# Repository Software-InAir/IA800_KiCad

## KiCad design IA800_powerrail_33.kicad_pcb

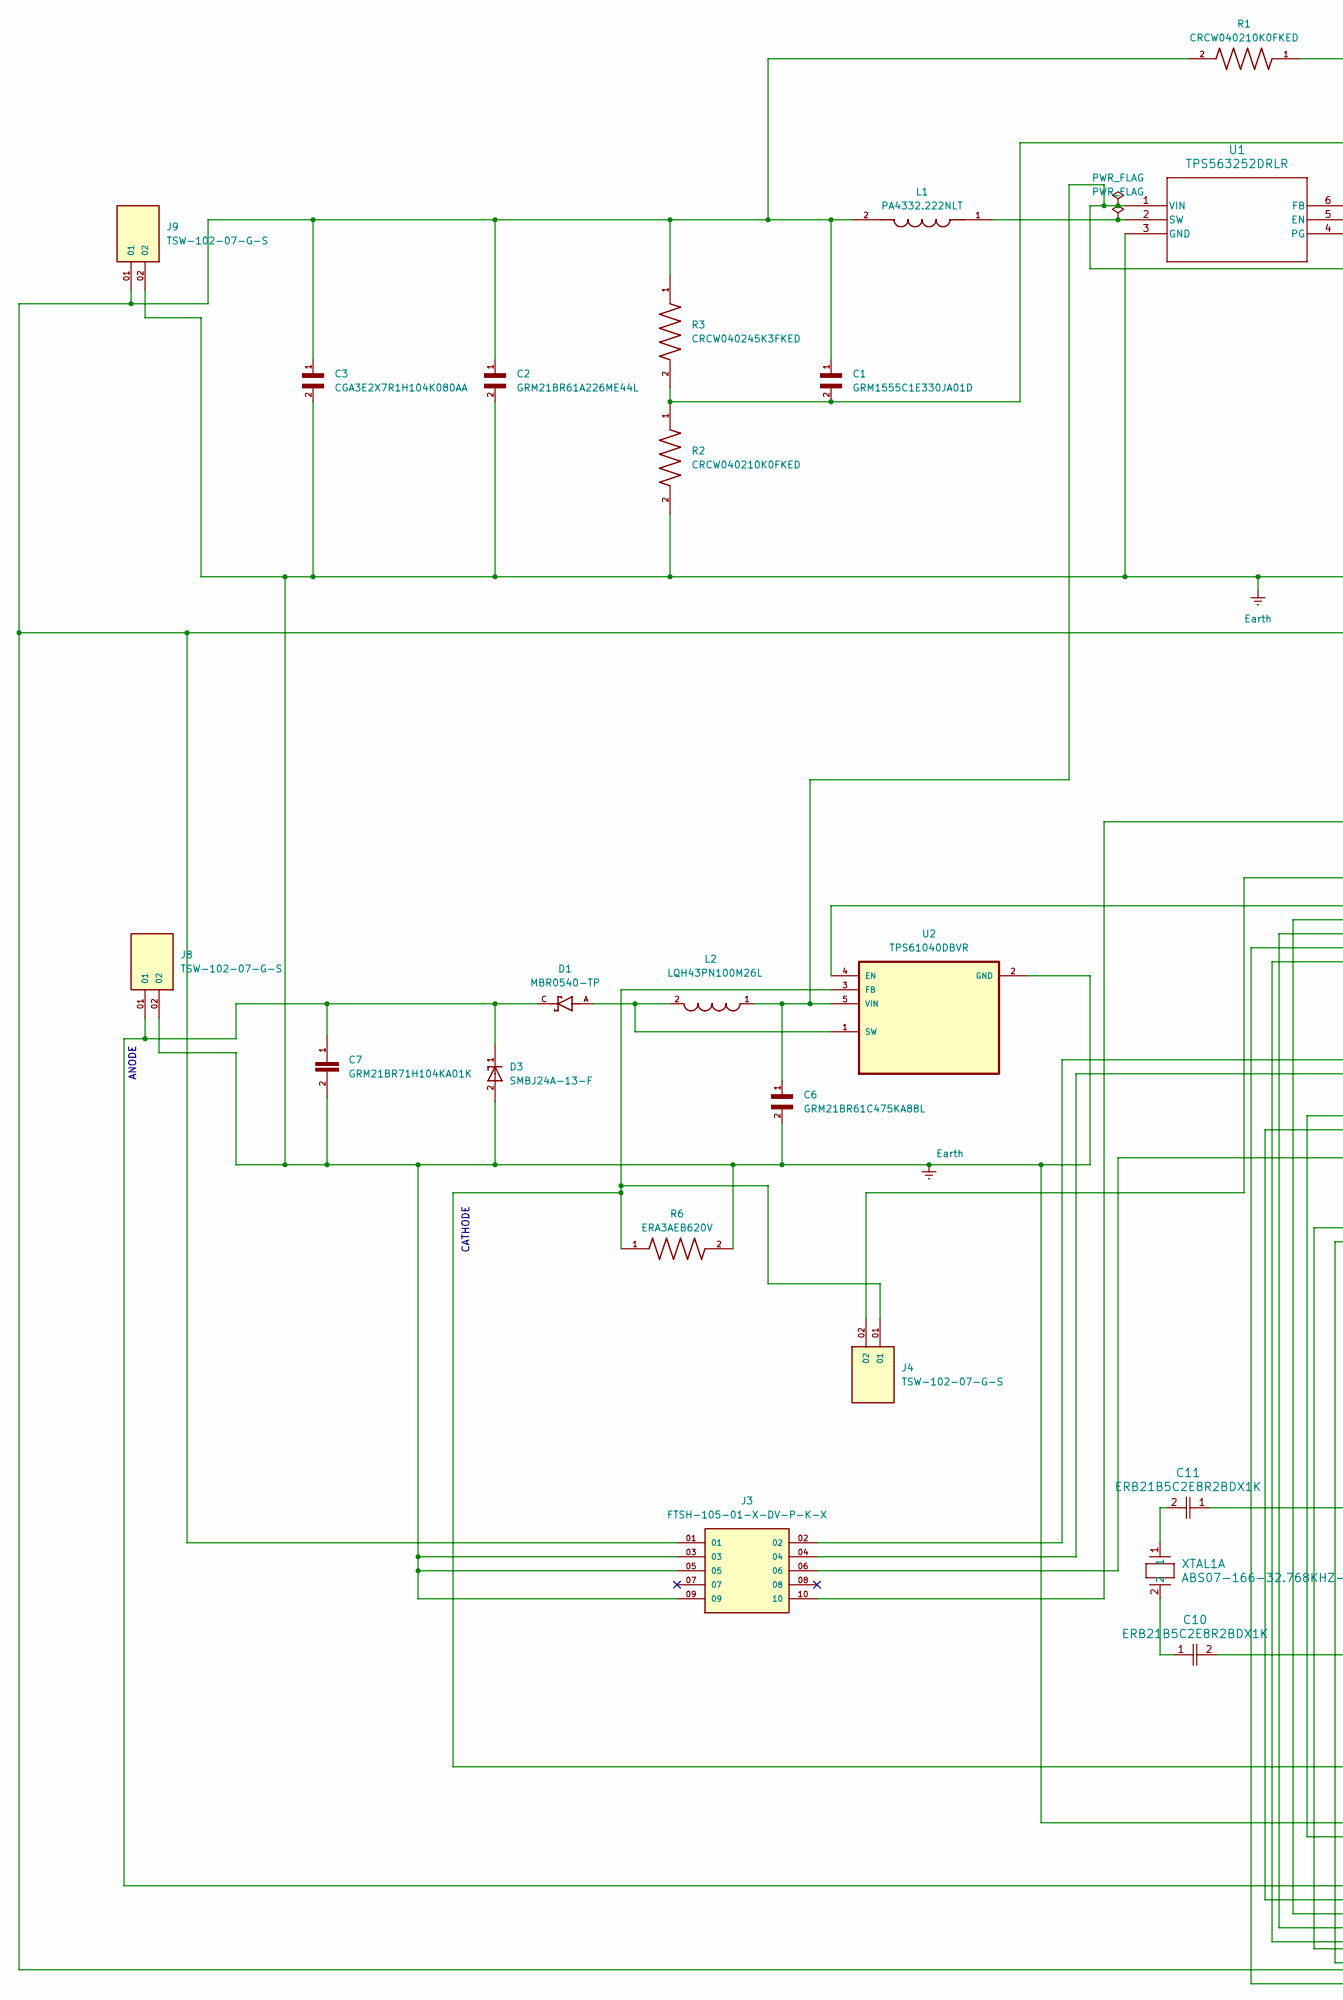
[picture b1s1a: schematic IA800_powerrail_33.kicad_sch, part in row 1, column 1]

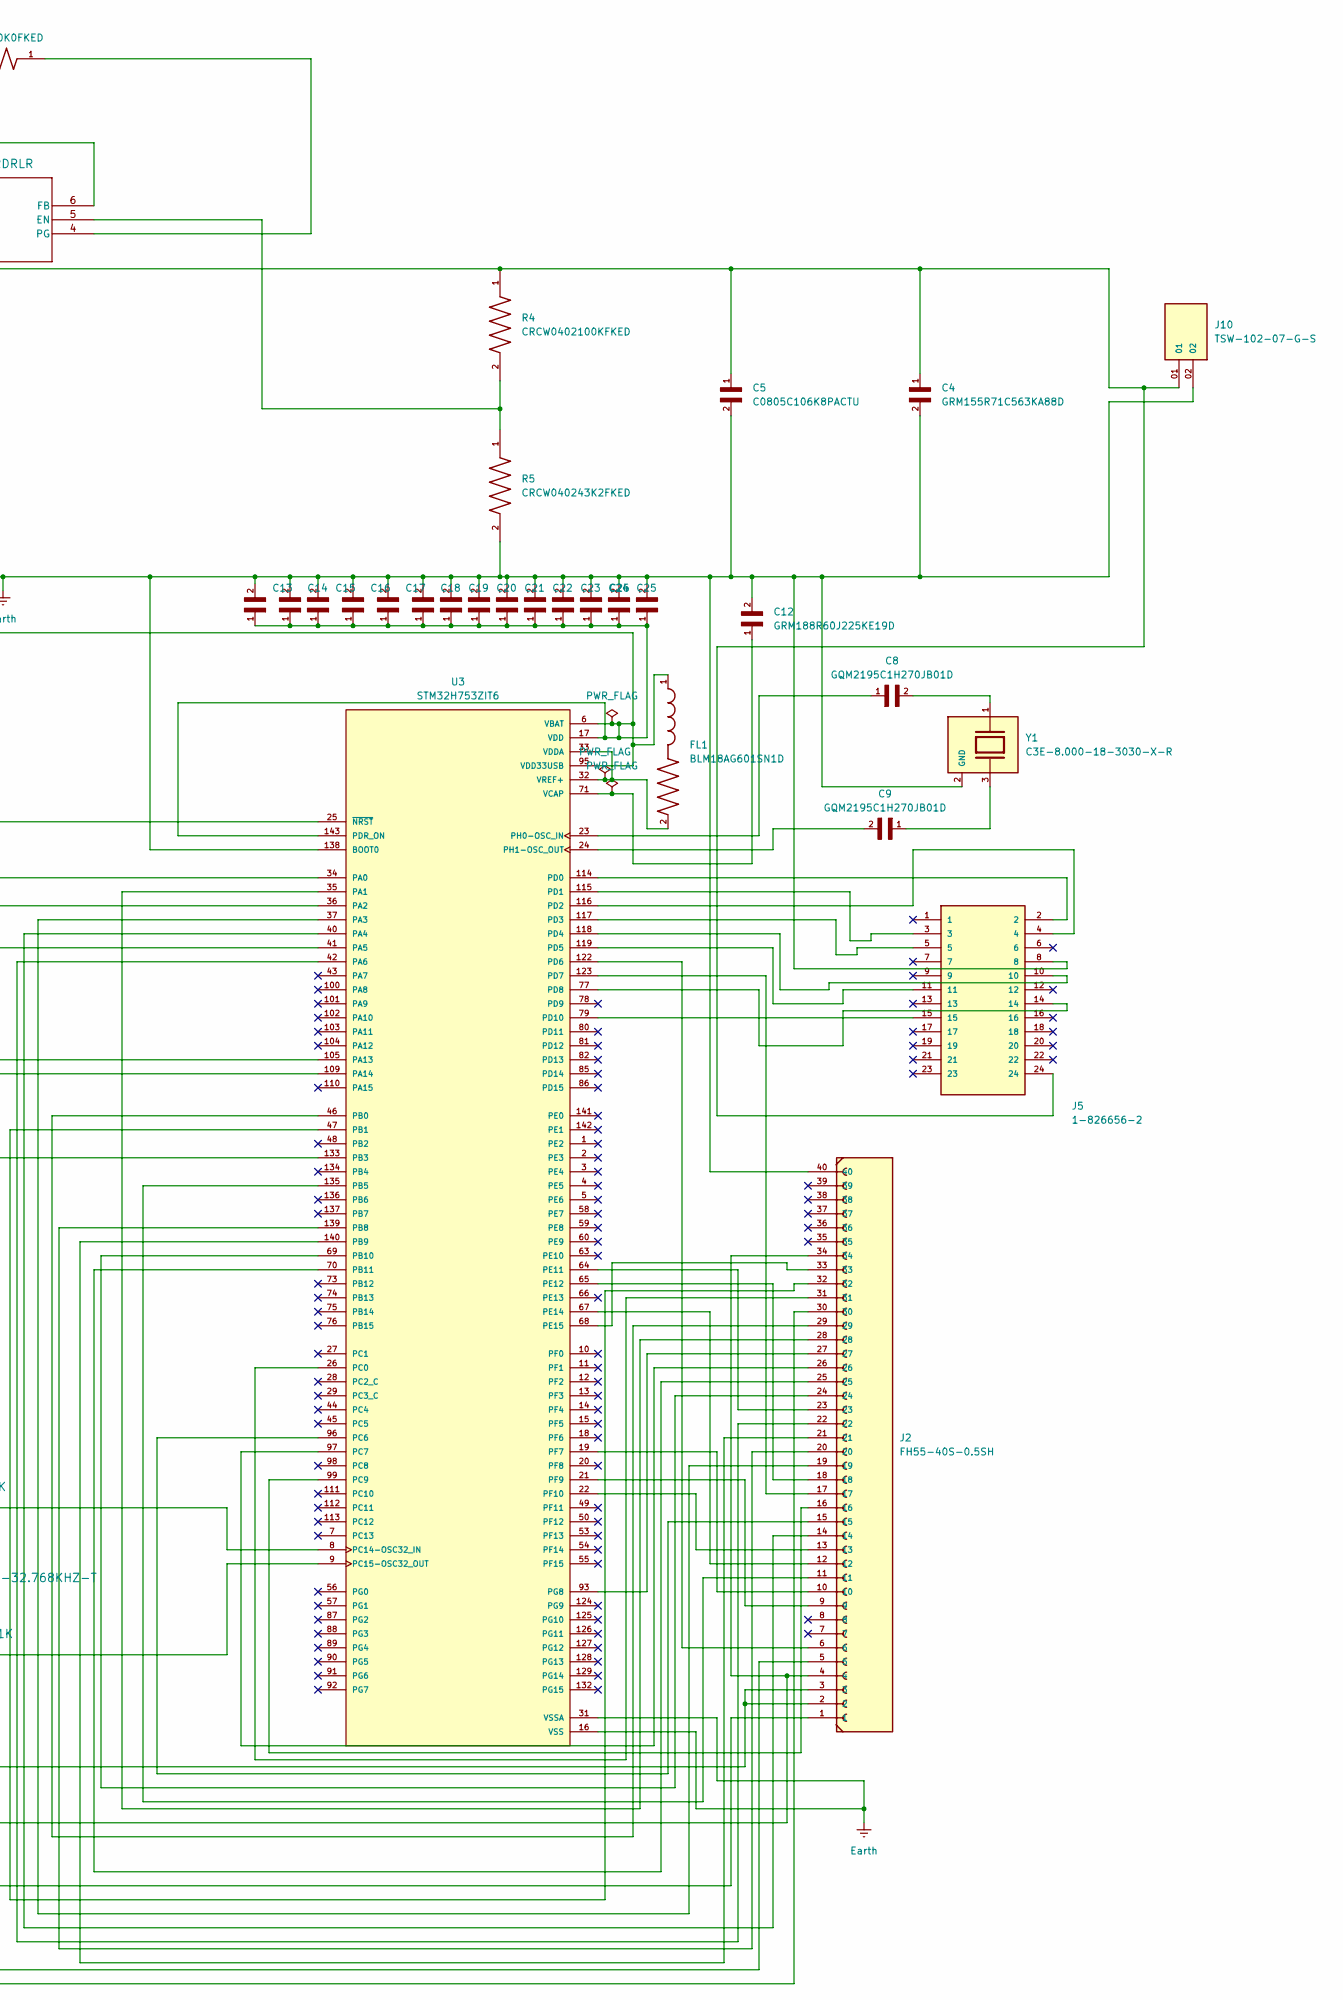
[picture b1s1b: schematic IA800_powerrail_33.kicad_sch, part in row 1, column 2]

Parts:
C1: GRM1555C1E330JA01D; CAPC1005X55N
C2: GRM21BR61A226ME44L; CAPC2012X145N
C3: CGA3E2X7R1H104K080AA; CAPC1608X90N
C4: GRM155R71C563KA88D; CAPC1005X55N
C5: C0805C106K8PACTU; CAPC2012X88N
C6: GRM21BR61C475KA88L; CAPC2012X135N
C7: GRM21BR71H104KA01K; CAPC2012X135
C8, C9: GQM2195C1H270JB01D; CAPC2012X95N
C10, C11: ERB21B5C2E8R2BDX1K; CAP_ERB21_MUR
C12: GRM188R60J225KE19D; CAPC1608X90N
C13, C14, C15, C16, C17, C18, C19, C20, C21, C22, C23, C24, C25, C26: CL05B104KO5NNNC; CAPC1005X55N
D1: MBR0540-TP; DIO_MBR0540-TP; PARTREV 3
D3: SMBJ24A-13-F; DIOM5336X250N; PARTREV 20 - 2
FL1: BLM18AG601SN1D; BEADC1608X95N
J2: FH55-40S-0.5SH; HRS_FH55-40S-0.5SH
J3: FTSH-105-01-X-DV-P-K-X; SAMTEC_FTSH-105-01-X-DV-P-K-X; PARTREV H
J4, J8, J9, J10: TSW-102-07-G-S; SAMTEC_TSW-102-07-G-S
J5: 1-826656-2; TE_1-826656-2; PARTREV R
L1: PA4332.222NLT; IND_PA4332.222NLT; PARTREV 12/23
L2: LQH43PN100M26L; IND_LQH43PN100M26L; PARTREV N/A
R1, R2: CRCW040210K0FKED; RESC1005X40N
R3: CRCW040245K3FKED; RESC1005X40N
R4: CRCW0402100KFKED; RESC1005X40N
R5: CRCW040243K2FKED; RESC1005X40N
R6: ERA3AEB620V; RES_ERA3AEB620V; PARTREV 3/1/2020
U1: TPS563252DRLR; SOT6_DRL_TEX
U2: TPS61040DBVR; SOT95P280X145-5N
U3: STM32H753ZIT6; QFP50P2200X2200X160-144N; PARTREV 7
XTAL1: ABS07-166-32.768KHZ-T; XTAL_ABS07-166-32.768KHZ-T_ABR
Y1: C3E-8.000-18-3030-X-R; XTAL_C3E-8.000-18-3030-X-R; PARTREV August 01, 2022

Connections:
Earth: C2.2, C3.2, C4.2, C5.2, C6.2, C7.2, C12.2, C13.2, C14.2, C15.2, C16.2, C17.2, C18.2, C19.2, C20.2, C21.2, C22.2, C23.2, C24.2, C25.2, C26.2, D3.2, J2.4, J2.34, J2.40, J3.03, J3.05, J3.09, J5.8, J8.02, J9.02, J10.02, R2.2, R5.2, R6.2, U1.3 (GND), U2.2 (GND), U3.16 (VSS), U3.31 (VSSA), U3.38 (VSS), U3.51 (VSS), U3.61 (VSS), U3.83 (VSS), U3.94 (VSS), U3.107 (VSS), U3.120 (VSS), U3.130 (VSS), U3.138 (BOOT0), Y1.2 (GND), Y1.4 (GND)
unnamed: C7.1, D1.C, D3.1, J2.1, J8.01
unnamed: C8.2, Y1.1
unnamed: C9.1, Y1.3
unnamed: C10.1, XTAL1.2
unnamed: C11.2, XTAL1.1
unnamed: R4.2, R5.1, U1.5 (EN)
unnamed: C1.2, R2.1, R3.2, U1.6 (FB)
unnamed: R1.1, U1.4 (PG)
unnamed: L1.1, U1.2 (SW)
unnamed: C4.1, C5.1, C6.1, J5.24, J10.01, L2.1, R4.1, U1.1 (VIN), U2.5 (VIN)
unnamed: U2.4 (EN), U3.36 (PA2)
unnamed: J2.2, J2.3, J4.01, R6.1, U2.3 (FB)
unnamed: D1.A, L2.2, U2.1 (SW)
unnamed: J4.02, U3.34 (PA0)
unnamed: J2.28, U3.35 (PA1)
unnamed: J2.19, U3.37 (PA3)
unnamed: J2.14, U3.40 (PA4)
unnamed: J2.30, U3.41 (PA5)
unnamed: J2.22, U3.42 (PA6)
unnamed: J3.02, U3.105 (PA13)
unnamed: J3.04, U3.109 (PA14)
unnamed: J2.29, U3.46 (PB0)
unnamed: J2.32, U3.47 (PB1)
unnamed: J3.06, U3.133 (PB3)
unnamed: J2.11, U3.135 (PB5)
unnamed: J2.20, U3.139 (PB8)
unnamed: J2.21, U3.140 (PB9)
unnamed: J2.24, U3.69 (PB10)
unnamed: J2.25, U3.70 (PB11)
unnamed: J2.31, U3.26 (PC0)
unnamed: J2.15, U3.96 (PC6)
unnamed: J2.26, U3.97 (PC7)
unnamed: J2.16, U3.99 (PC9)
unnamed: C11.1, U3.8 (PC14-OSC32_IN)
unnamed: C10.2, U3.9 (PC15-OSC32_OUT)
unnamed: J5.2, U3.114 (PD0)
unnamed: J5.3, U3.115 (PD1)
unnamed: J5.4, U3.116 (PD2)
unnamed: J5.5, U3.117 (PD3)
unnamed: J5.10, U3.118 (PD4)
unnamed: J5.11, U3.119 (PD5)
unnamed: J2.6, U3.122 (PD6)
unnamed: J2.17, U3.123 (PD7)
unnamed: J5.14, U3.77 (PD8)
unnamed: J5.15, U3.79 (PD10)
unnamed: J2.23, U3.64 (PE11)
unnamed: J2.18, U3.65 (PE12)
unnamed: J2.12, U3.67 (PE14)
unnamed: J2.33, U3.68 (PE15)
unnamed: J2.10, U3.19 (PF7)
unnamed: J2.9, U3.21 (PF9)
unnamed: J2.13, U3.22 (PF10)
unnamed: J2.27, U3.93 (PG8)
unnamed: C8.1, U3.23 (PH0-OSC_IN)
unnamed: C9.2, U3.24 (PH1-OSC_OUT)
unnamed: FL1.2, U3.32 (VREF+), U3.33 (VDDA)
unnamed: J3.10, U3.25 (~NRST)
VCAP: C12.1, U3.71 (VCAP), U3.106 (VCAP)
VDD: C1.1, C2.1, C3.1, C13.1, C14.1, C15.1, C16.1, C17.1, C18.1, C19.1, C20.1, C21.1, C22.1, C23.1, C24.1, C25.1, C26.1, FL1.1, J2.5, J3.01, J9.01, L1.2, R1.2, R3.1, U3.6 (VBAT), U3.17 (VDD), U3.30 (VDD), U3.39 (VDD), U3.52 (VDD), U3.62 (VDD), U3.72 (VDD), U3.84 (VDD), U3.95 (VDD33USB), U3.108 (VDD), U3.121 (VDD), U3.131 (VDD), U3.143 (PDR_ON), U3.144 (VDD)

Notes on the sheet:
CATHODE
ANODE

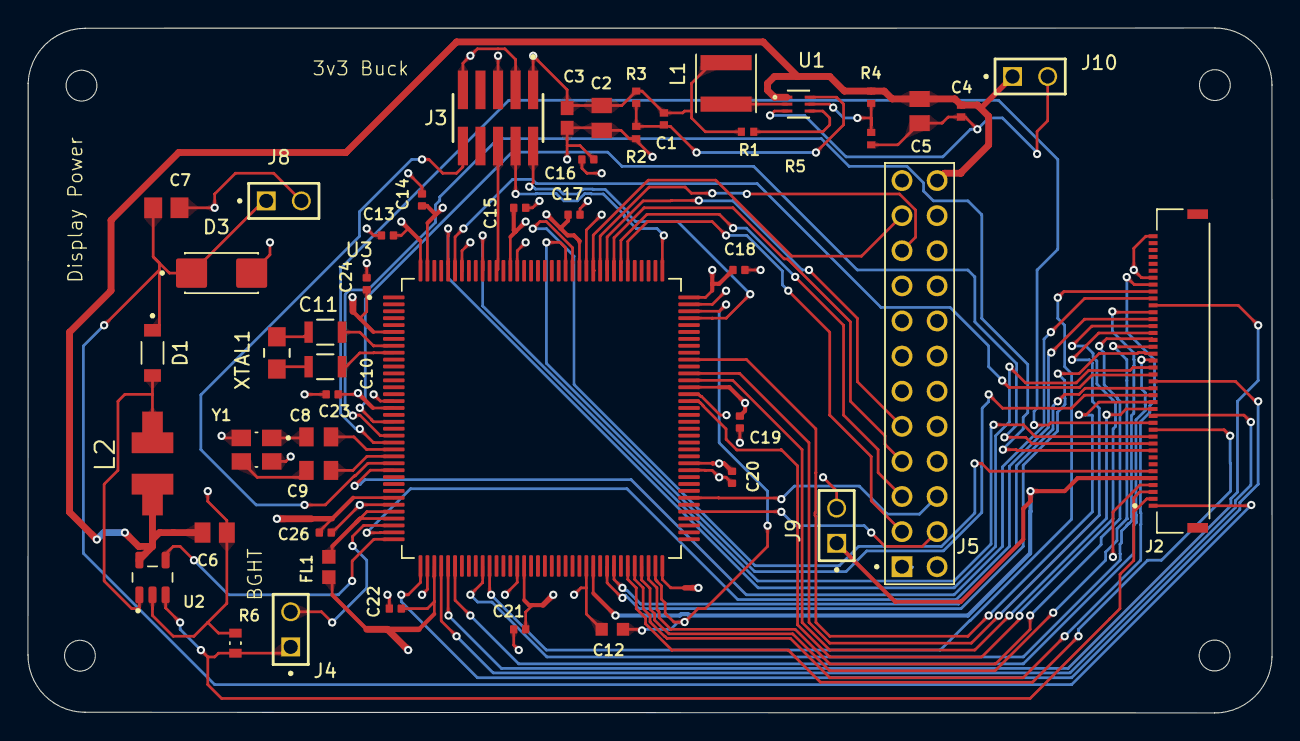
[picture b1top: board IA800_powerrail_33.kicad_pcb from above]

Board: 4 copper layers, 90.0 x 49.6 mm, 48 parts (0 on the bottom side), 60 nets.

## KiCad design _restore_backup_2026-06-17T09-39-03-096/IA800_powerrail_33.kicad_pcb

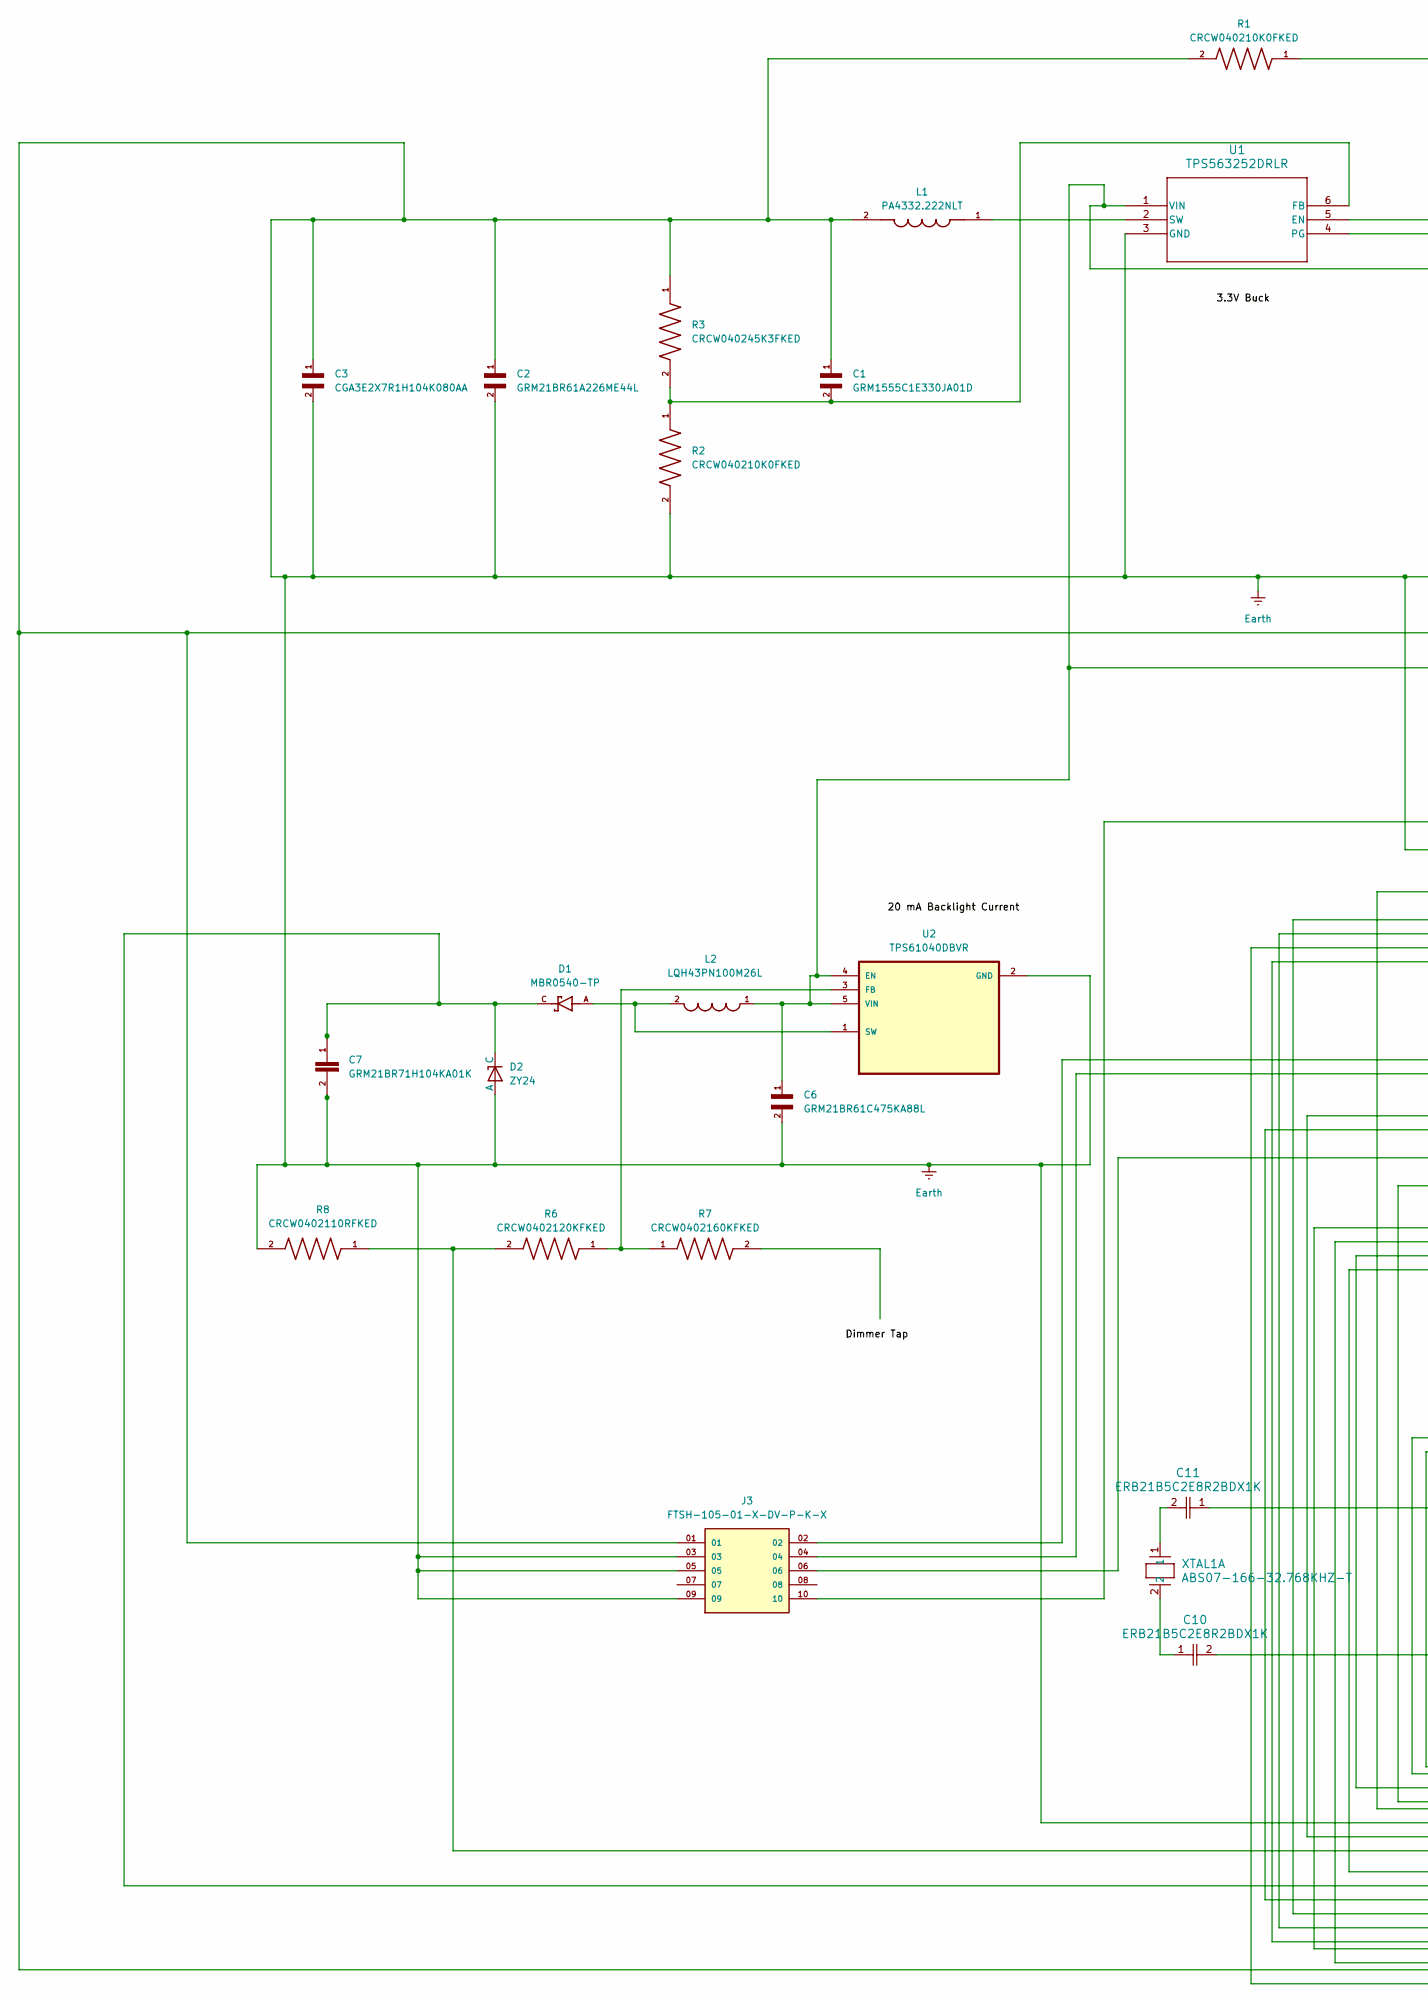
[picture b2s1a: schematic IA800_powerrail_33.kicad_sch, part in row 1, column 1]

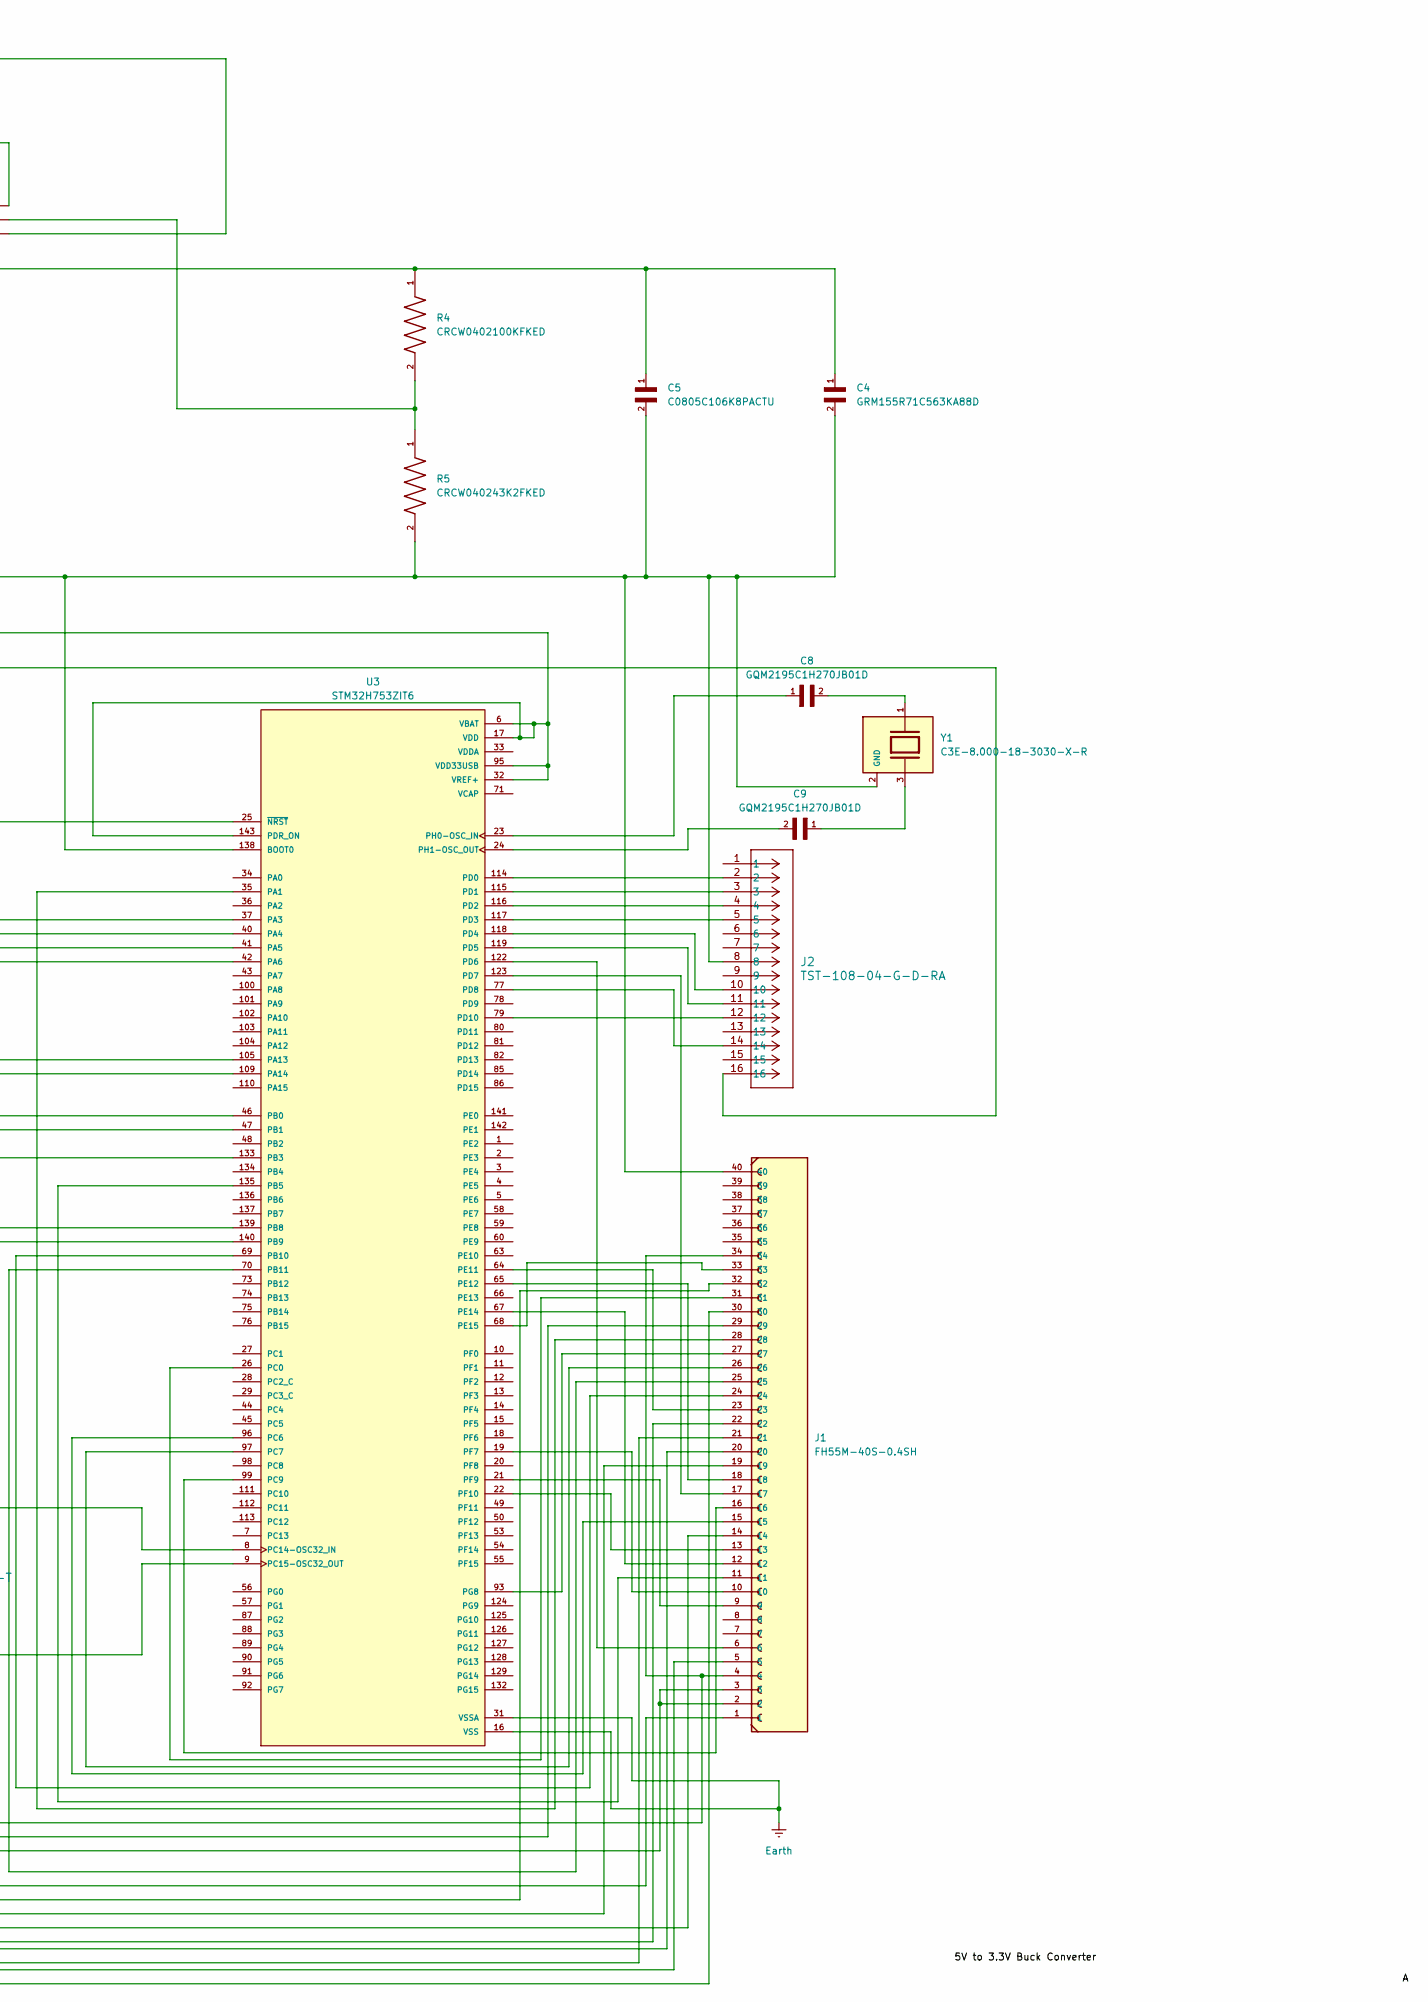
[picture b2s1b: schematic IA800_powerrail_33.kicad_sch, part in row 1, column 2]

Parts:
C1: GRM1555C1E330JA01D; CAPC1005X55N
C2: GRM21BR61A226ME44L; CAPC2012X145N
C3: CGA3E2X7R1H104K080AA; CAPC1608X90N
C4: GRM155R71C563KA88D; CAPC1005X55N
C5: C0805C106K8PACTU; CAPC2012X88N
C6: GRM21BR61C475KA88L; CAPC2012X135N
C7: GRM21BR71H104KA01K; CAPC2012X135
C8, C9: GQM2195C1H270JB01D; CAPC2012X95N
C10, C11: ERB21B5C2E8R2BDX1K; CAP_ERB21_MUR
D1: MBR0540-TP; DIO_MBR0540-TP; PARTREV 3
D2: ZY24; P1_DO-41
J1: FH55M-40S-0.4SH; HRS_FH55M-40S-0.4SH
J2: TST-108-04-G-D-RA; CONN_TST-108-XX-X-D-RA_SAI
J3: FTSH-105-01-X-DV-P-K-X; SAMTEC_FTSH-105-01-X-DV-P-K-X; PARTREV H
L1: PA4332.222NLT; IND_PA4332.222NLT; PARTREV 12/23
L2: LQH43PN100M26L; IND_LQH43PN100M26L; PARTREV N/A
R1, R2: CRCW040210K0FKED; RESC1005X40N
R3: CRCW040245K3FKED; RESC1005X40N
R4: CRCW0402100KFKED; RESC1005X40N
R5: CRCW040243K2FKED; RESC1005X40N
R6: CRCW0402120KFKED; RESC1005X40N
R7: CRCW0402160KFKED; RESC1005X40N
R8: CRCW0402110RFKED; RESC1005X40N
U1: TPS563252DRLR; SOT6_DRL_TEX
U2: TPS61040DBVR; SOT95P280X145-5N
U3: STM32H753ZIT6; QFP50P2200X2200X160-144N; PARTREV 7
XTAL1: ABS07-166-32.768KHZ-T; XTAL_ABS07-166-32.768KHZ-T_ABR
Y1: C3E-8.000-18-3030-X-R; XTAL_C3E-8.000-18-3030-X-R; PARTREV August 01, 2022

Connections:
unnamed: C8.2, Y1.1
unnamed: C9.1, Y1.3
unnamed: C10.1, XTAL1.2
unnamed: C11.2, XTAL1.1
unnamed: C7.1, D1.C, D2.1 (C), J1.1
unnamed: J1.2, J1.3, R6.2, R8.1
unnamed: R4.2, R5.1, U1.5 (EN)
unnamed: C1.2, R2.1, R3.2, U1.6 (FB)
unnamed: R1.1, U1.4 (PG)
unnamed: L1.1, U1.2 (SW)
unnamed: C4.1, C5.1, C6.1, J2.16, L2.1, R4.1, U1.1 (VIN), U2.4 (EN), U2.5 (VIN)
unnamed: R6.1, R7.1, U2.3 (FB)
unnamed: D1.A, L2.2, U2.1 (SW)
unnamed: J1.28, U3.35 (PA1)
unnamed: J1.19, U3.37 (PA3)
unnamed: J1.14, U3.40 (PA4)
unnamed: J1.30, U3.41 (PA5)
unnamed: J1.22, U3.42 (PA6)
unnamed: J3.02, U3.105 (PA13)
unnamed: J3.04, U3.109 (PA14)
unnamed: J1.29, U3.46 (PB0)
unnamed: J1.32, U3.47 (PB1)
unnamed: J3.06, U3.133 (PB3)
unnamed: J1.11, U3.135 (PB5)
unnamed: J1.20, U3.139 (PB8)
unnamed: J1.21, U3.140 (PB9)
unnamed: J1.24, U3.69 (PB10)
unnamed: J1.25, U3.70 (PB11)
unnamed: J1.31, U3.26 (PC0)
unnamed: J1.15, U3.96 (PC6)
unnamed: J1.26, U3.97 (PC7)
unnamed: J1.16, U3.99 (PC9)
unnamed: C11.1, U3.8 (PC14-OSC32_IN)
unnamed: C10.2, U3.9 (PC15-OSC32_OUT)
unnamed: J2.2, U3.114 (PD0)
unnamed: J2.3, U3.115 (PD1)
unnamed: J2.4, U3.116 (PD2)
unnamed: J2.5, U3.117 (PD3)
unnamed: J2.10, U3.118 (PD4)
unnamed: J2.11, U3.119 (PD5)
unnamed: J1.6, U3.122 (PD6)
unnamed: J1.17, U3.123 (PD7)
unnamed: J2.14, U3.77 (PD8)
unnamed: J2.12, U3.79 (PD10)
unnamed: J1.23, U3.64 (PE11)
unnamed: J1.18, U3.65 (PE12)
unnamed: J1.12, U3.67 (PE14)
unnamed: J1.33, U3.68 (PE15)
unnamed: J1.10, U3.19 (PF7)
unnamed: J1.9, U3.21 (PF9)
unnamed: J1.13, U3.22 (PF10)
unnamed: J1.27, U3.93 (PG8)
unnamed: C8.1, U3.23 (PH0-OSC_IN)
unnamed: C9.2, U3.24 (PH1-OSC_OUT)
unnamed: J3.10, U3.25 (~NRST)
VCAP: U3.71 (VCAP), U3.106 (VCAP); also elsewhere on the board

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
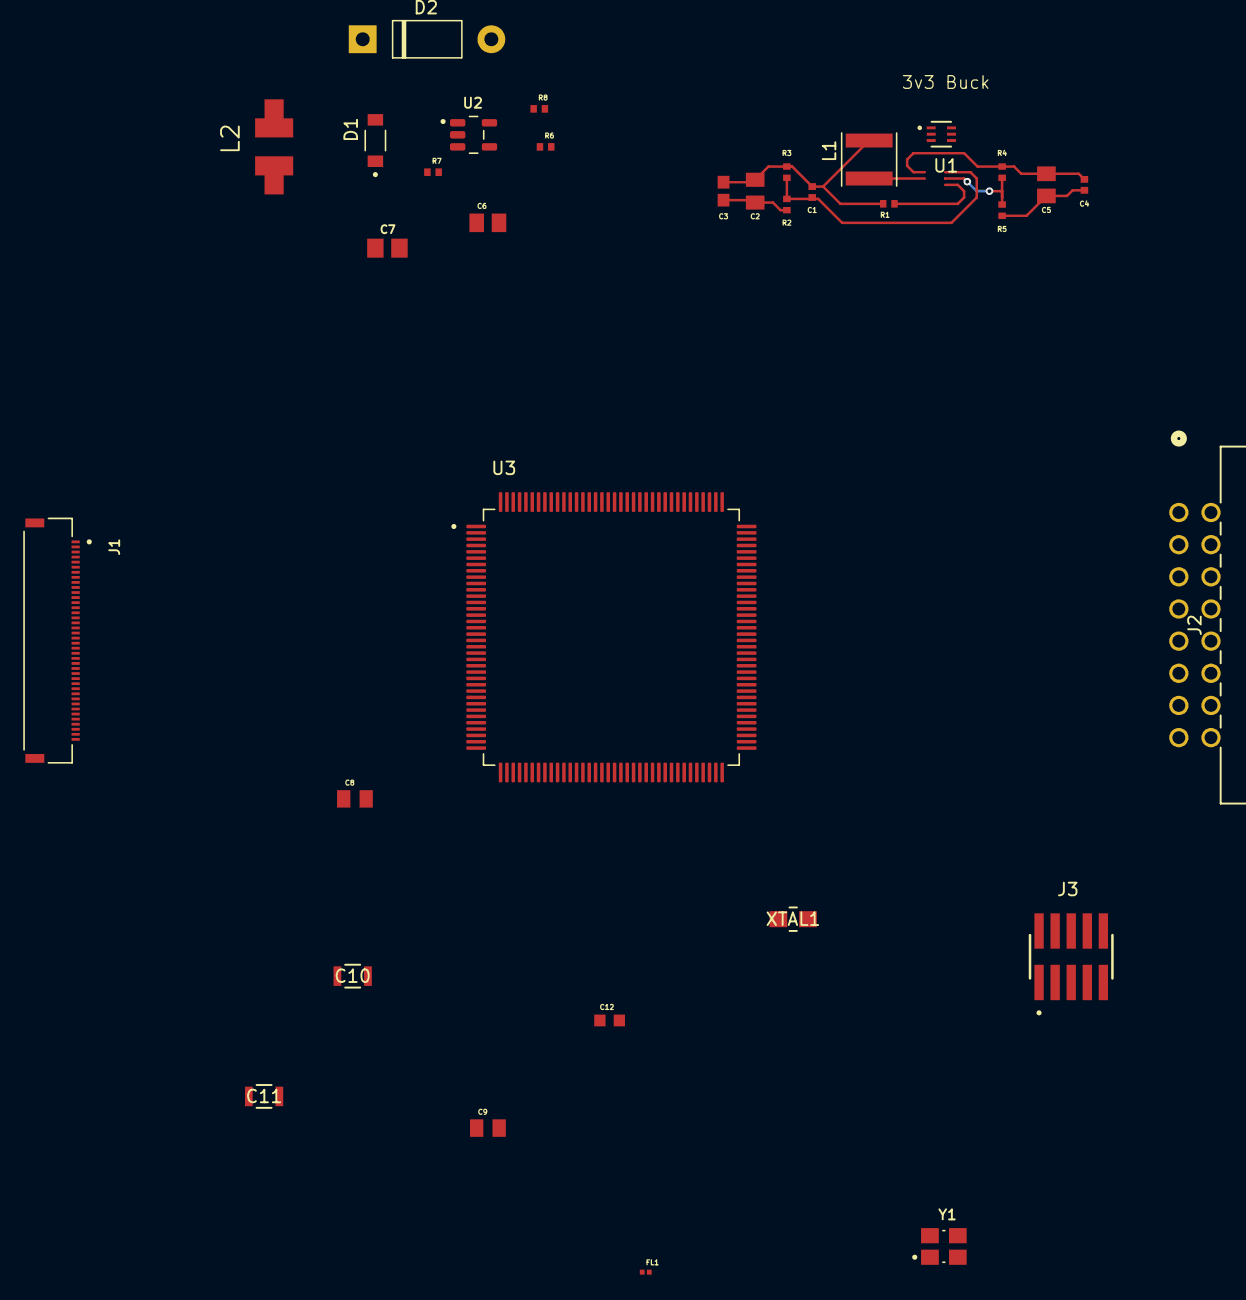
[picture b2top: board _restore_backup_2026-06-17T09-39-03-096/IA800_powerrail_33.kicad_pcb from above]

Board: 2 copper layers, 33 parts (0 on the bottom side), 59 nets.

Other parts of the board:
C12: GRM188R60J225KE19D; CAPC1608X90N
FL1: BLM03EB500SZ1D; BEADC0603X33N

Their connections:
VCAP: C12.1; also elsewhere on the board
